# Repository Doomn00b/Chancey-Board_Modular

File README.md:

# Chancey-Board_Modular
A fork of Riskable's great Hall-effect Keyboard, but 100% and modular.

Planned changes are a new RISC-V micro-controller, with more IO, since a 100% implementation will require more.

# The original Riskey-board

Link to repository:
https://github.com/riskable/void_switch_65_pct

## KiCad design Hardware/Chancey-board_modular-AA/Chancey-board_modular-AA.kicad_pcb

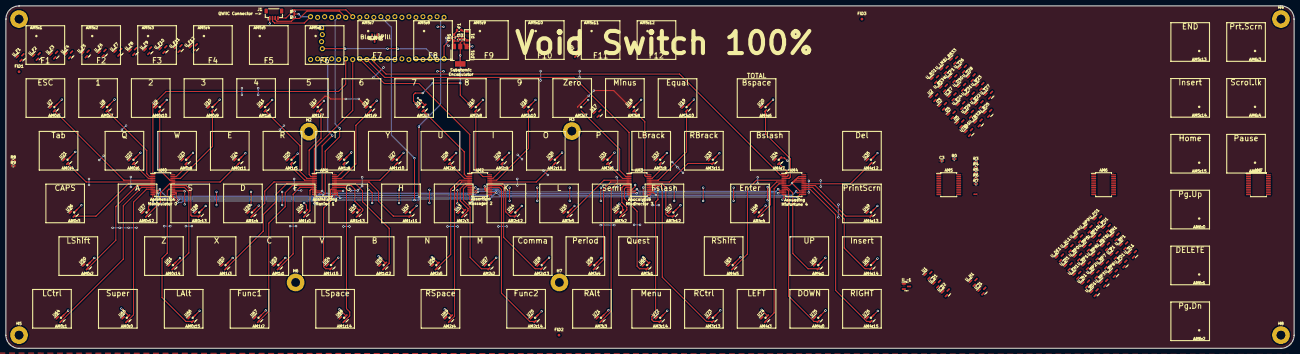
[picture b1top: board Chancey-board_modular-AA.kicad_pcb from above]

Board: 2 copper layers, 465.9 x 123.8 mm, 268 parts (1 on the bottom side), 139 nets.

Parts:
AM0, AM1, AM2, AM3, AM4, AM5, AM6, AM7: CD74HC4067SM; SSOP-24_5.3x8.2mm_P0.65mm
AM0:0: Super; VoidSwitch_1u_SMD
AM0:1: LCtrl; VoidSwitch_1u_SMD
AM0:2: LShift; VoidSwitch_1u_SMD
AM0:3: CAPS; VoidSwitch_1u_SMD
AM0:4: Tab; VoidSwitch_1u_SMD
AM0:5: ESC; VoidSwitch_1u_SMD
AM0:6: Q; VoidSwitch_1u_SMD
AM0:7: 1; VoidSwitch_1u_SMD
AM0:8: W; VoidSwitch_1u_SMD
AM0:9: 3; VoidSwitch_1u_SMD
AM0:10: 2; VoidSwitch_1u_SMD
AM0:11: E; VoidSwitch_1u_SMD
AM0:12: A; VoidSwitch_1u_SMD
AM0:13: S; VoidSwitch_1u_SMD
AM0:14: Z; VoidSwitch_1u_SMD
AM0:15: LAlt; VoidSwitch_1u_SMD
AM1:0: F; VoidSwitch_1u_SMD
AM1:1: C; VoidSwitch_1u_SMD
AM1:2: Func1; VoidSwitch_1u_SMD
AM1:3: X; VoidSwitch_1u_SMD
AM1:4: D; VoidSwitch_1u_SMD
AM1:5: R; VoidSwitch_1u_SMD
AM1:6: 4; VoidSwitch_1u_SMD
AM1:7: 5; VoidSwitch_1u_SMD
AM1:8: T; VoidSwitch_1u_SMD
AM1:9: 6; VoidSwitch_1u_SMD
AM1:10: Y; VoidSwitch_1u_SMD
AM1:11: H; VoidSwitch_1u_SMD
AM1:12: B; VoidSwitch_1u_SMD
AM1:13: G; VoidSwitch_1u_SMD
AM1:14: LSpace; VoidSwitch_1u_SMD
AM1:15: V; VoidSwitch_1u_SMD
AM2:2: M; VoidSwitch_1u_SMD
AM2:3: J; VoidSwitch_1u_SMD
AM2:4: RSpace; VoidSwitch_1u_SMD
AM2:5: N; VoidSwitch_1u_SMD
AM2:6: U; VoidSwitch_1u_SMD
AM2:7: 7; VoidSwitch_1u_SMD
AM2:8: 8; VoidSwitch_1u_SMD
AM2:9: I; VoidSwitch_1u_SMD
AM2:10: 9; VoidSwitch_1u_SMD
AM2:11: O; VoidSwitch_1u_SMD
AM2:12: K; VoidSwitch_1u_SMD
AM2:13: Comma; VoidSwitch_1u_SMD
AM2:14: Func2; VoidSwitch_1u_SMD
AM3:1: Quest; VoidSwitch_1u_SMD
AM3:2: Semi; VoidSwitch_1u_SMD
AM3:3: RAlt; VoidSwitch_1u_SMD
AM3:4: Period; VoidSwitch_1u_SMD
AM3:5: L; VoidSwitch_1u_SMD
AM3:6: P; VoidSwitch_1u_SMD
AM3:7: Zero; VoidSwitch_1u_SMD
AM3:8: Minus; VoidSwitch_1u_SMD
AM3:9: LBrack; VoidSwitch_1u_SMD
AM3:10: Equal; VoidSwitch_1u_SMD
AM3:11: RBrack; VoidSwitch_1u_SMD
AM3:12: Fslash; VoidSwitch_1u_SMD
AM3:13: RCtrl; VoidSwitch_1u_SMD
AM3:14: Menu; VoidSwitch_1u_SMD
AM4:0: DOWN; VoidSwitch_1u_SMD
AM4:1: UP; VoidSwitch_1u_SMD
AM4:3: LEFT; VoidSwitch_1u_SMD
AM4:4: Enter; VoidSwitch_1u_SMD
AM4:5: RShift; VoidSwitch_1u_SMD
AM4:6: Bspace; VoidSwitch_1u_SMD
AM4:7: Bslash; VoidSwitch_1u_SMD
AM4:12: Del; VoidSwitch_1u_SMD
AM4:13: PrintScrn; VoidSwitch_1u_SMD
AM4:14, AM5:14: Insert; VoidSwitch_1u_SMD
AM4:15: RIGHT; VoidSwitch_1u_SMD
AM5:1: F1; VoidSwitch_1u_SMD
AM5:2: F2; VoidSwitch_1u_SMD
AM5:3: F3; VoidSwitch_1u_SMD
AM5:4: F4; VoidSwitch_1u_SMD
AM5:5: F5; VoidSwitch_1u_SMD
AM5:6: F6; VoidSwitch_1u_SMD
AM5:7: F7; VoidSwitch_1u_SMD
AM5:8: F8; VoidSwitch_1u_SMD
AM5:9: F9; VoidSwitch_1u_SMD
AM5:10: F10; VoidSwitch_1u_SMD
AM5:11: F11; VoidSwitch_1u_SMD
AM5:12: F12; VoidSwitch_1u_SMD
AM5:13: END; VoidSwitch_1u_SMD
AM5:15: Home; VoidSwitch_1u_SMD
AM6:0: Pg.Up; VoidSwitch_1u_SMD
AM6:1: DELETE; VoidSwitch_1u_SMD
AM6:2: Pg.Dn; VoidSwitch_1u_SMD
AM6:3: Prt.Scrn; VoidSwitch_1u_SMD
AM6:4: Scrol.lk; VoidSwitch_1u_SMD
AM6:5: Pause; VoidSwitch_1u_SMD
C1, C2, C3: 10u; C_0402_1005Metric
D1: B5819W; D_SOD-123
F1: 500mA; Fuse_0603_1608Metric
FB1: 100 @ 100 MHz; L_0805_2012Metric
FID1, FID2, FID3: Fiducial; Fiducial_1mm_Mask2mm
H1, H2, H3, H4, H5, H6, H7, H8: MountingHole_Pad; MountingHole_3.2mm_M3_Pad
J1: QWIIC; JST_SH_BM04B-SRSS-TB_1x04-1MP_P1.00mm_Vertical
LDO1: AMS1117-3.3; SOT-223-3_TabPin2
NT1: NetTie_2; NetTie-2_SMD_Pad0.5mm
QR*****: https://github.com/riskable/void_switch; VoidSwitch_Repo_QR_0.5mm
R0, R1, R2, R3, R4, R5, R6, R7, R8, R9: 2k2; R_0402_1005Metric
U0, U1, U2, U3, U4, U5, U6, U7, U8, U9, U10, U11, U12, U13, U14, U15, U16, U17, U18, U19, U20, U21, U22, U23, U24, U25, U26, U27, U28, U29, U30, U31, U32, U33, U34, U35, U36, U37, U38, U39, U40, U41, U42, U43, U44, U45, U46, U47, U48, U49, U50, U51, U52, U53, U54, U55, U56, U57, U58, U59, U60, U61, U62, U63, U64, U65, U66, U67, U68, U69, U70, U71, U72, U73, U74, U75, U76: Hall_Sensor; SOT-23
UTab1: Hall_Sensor; SOT-23
U_BP1: BlackPill_STLINK
U_BS1, U_BS34: Hall_Sensor; SOT-23
U_D1, U_D2: Hall_Sensor; SOT-23
U_DE1: Hall_Sensor; SOT-23
U_Di1: Hall_Sensor; SOT-23
U_E7, U_E24: Hall_Sensor; SOT-23
U_EN1: Hall_Sensor; SOT-23
U_F1, U_F2, U_F3, U_F4, U_F5, U_F6, U_F7, U_F8, U_F9, U_F10, U_F11, U_F12: Hall_Sensor; SOT-23
U_H1: Hall_Sensor; SOT-23
U_I1, U_I29: Hall_Sensor; SOT-23
U_In1: Hall_Sensor; SOT-23
U_LB32: Hall_Sensor; SOT-23
U_LM1: Hall_Sensor; SOT-23
U_LP1: Hall_Sensor; SOT-23
U_ND1: Hall_Sensor; SOT-23
U_NL1: Hall_Sensor; SOT-23
U_NP0, U_NP1, U_NP2, U_NP3, U_NP4, U_NP5, U_NP6, U_NP7, U_NP8, U_NP9, U_NP10: Hall_Sensor; SOT-23
U_NpT1: Hall_Sensor; SOT-23
U_O30: Hall_Sensor; SOT-23
U_P1, U_P31: Hall_Sensor; SOT-23
U_PD1: Hall_Sensor; SOT-23
U_PS1: Hall_Sensor; SOT-23
U_PU1: Hall_Sensor; SOT-23
U_Q22: Hall_Sensor; SOT-23
U_R25: Hall_Sensor; SOT-23
U_RB33: Hall_Sensor; SOT-23
U_RM1: Hall_Sensor; SOT-23
U_RP1: Hall_Sensor; SOT-23
U_SL1: Hall_Sensor; SOT-23
U_T26: Hall_Sensor; SOT-23
U_U28: Hall_Sensor; SOT-23
U_W23: Hall_Sensor; SOT-23
U_Y27: Hall_Sensor; SOT-23
U_~1: Hall_Sensor; SOT-23

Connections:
+3.3V: AM0.24 (VCC), AM1.24 (VCC), AM2.24 (VCC), AM3.24 (VCC), AM4.24 (VCC), AM5.24 (VCC), AM6.24 (VCC), AM7.24 (VCC), C2.1, C3.1, NT1.2, U0.1 (VDD), U1.1 (VDD), U2.1 (VDD), U3.1 (VDD), U4.1 (VDD), U5.1 (VDD), U6.1 (VDD), U7.1 (VDD), U8.1 (VDD), U9.1 (VDD), U10.1 (VDD), U11.1 (VDD), U12.1 (VDD), U13.1 (VDD), U14.1 (VDD), U15.1 (VDD), U16.1 (VDD), U17.1 (VDD), U18.1 (VDD), U19.1 (VDD), U20.1 (VDD), U21.1 (VDD), U22.1 (VDD), U23.1 (VDD), U24.1 (VDD), U25.1 (VDD), U26.1 (VDD), U27.1 (VDD), U28.1 (VDD), U29.1 (VDD), U30.1 (VDD), U31.1 (VDD), U32.1 (VDD), U33.1 (VDD), U34.1 (VDD), U35.1 (VDD), U36.1 (VDD), U37.1 (VDD), U38.1 (VDD), U39.1 (VDD), U40.1 (VDD), U41.1 (VDD), U42.1 (VDD), U43.1 (VDD), U44.1 (VDD), U45.1 (VDD), U46.1 (VDD), U47.1 (VDD), U48.1 (VDD), U49.1 (VDD), U50.1 (VDD), U51.1 (VDD), U52.1 (VDD), U53.1 (VDD), U54.1 (VDD), U55.1 (VDD), U56.1 (VDD), U57.1 (VDD), U58.1 (VDD), U59.1 (VDD), U60.1 (VDD), U61.1 (VDD), U62.1 (VDD), U63.1 (VDD), U64.1 (VDD), U65.1 (VDD), U66.1 (VDD), U67.1 (VDD), U68.1 (VDD), U69.1 (VDD), U70.1 (VDD), U71.1 (VDD), U72.1 (VDD), U73.1 (VDD), U74.1 (VDD), U75.1 (VDD), U76.1 (VDD), UTab1.1 (VDD), U_BS1.1 (VDD), U_BS34.1 (VDD), U_D1.1 (VDD), U_D2.1 (VDD), U_DE1.1 (VDD), U_Di1.1 (VDD), U_E7.1 (VDD), U_E24.1 (VDD), U_EN1.1 (VDD), U_F1.1 (VDD), U_F2.1 (VDD), U_F3.1 (VDD), U_F4.1 (VDD), U_F5.1 (VDD), U_F6.1 (VDD), U_F7.1 (VDD), U_F8.1 (VDD), U_F9.1 (VDD), U_F10.1 (VDD), U_F11.1 (VDD), U_F12.1 (VDD), U_H1.1 (VDD), U_I1.1 (VDD), U_I29.1 (VDD), U_In1.1 (VDD), U_LB32.1 (VDD), U_LM1.1 (VDD), U_LP1.1 (VDD), U_ND1.1 (VDD), U_NL1.1 (VDD), U_NP0.1 (VDD), U_NP1.1 (VDD), U_NP2.1 (VDD), U_NP3.1 (VDD), U_NP4.1 (VDD), U_NP5.1 (VDD), U_NP6.1 (VDD), U_NP7.1 (VDD), U_NP8.1 (VDD), U_NP9.1 (VDD), U_NP10.1 (VDD), U_NpT1.1 (VDD), U_O30.1 (VDD), U_P1.1 (VDD), U_P31.1 (VDD), U_PD1.1 (VDD), U_PS1.1 (VDD), U_PU1.1 (VDD), U_Q22.1 (VDD), U_R25.1 (VDD), U_RB33.1 (VDD), U_RM1.1 (VDD), U_RP1.1 (VDD), U_SL1.1 (VDD), U_T26.1 (VDD), U_U28.1 (VDD), U_W23.1 (VDD), U_Y27.1 (VDD), U_~1.1 (VDD)
+3.3V_QWIIC: J1.2, R1.1, R2.1, U_BP1.20 (3V3)
+5V: D1.2 (A), U_BP1.40 (5V)
/AM0: AM0.1 (COM), U_BP1.26 (PA0)
/AM0:0: AM0.9 (I0), U65.2 (OUT)
/AM0:1: AM0.8 (I1), U64.2 (OUT)
/AM0:2: AM0.7 (I2), U50.2 (OUT)
/AM0:3: AM0.6 (I3), U36.2 (OUT)
/AM0:4: AM0.5 (I4), U21.2 (OUT), UTab1.2 (OUT)
/AM0:5: AM0.4 (I5), U_E7.2 (OUT)
/AM0:6: AM0.3 (I6), U22.2 (OUT), U_Q22.2 (OUT)
/AM0:7: AM0.2 (I7), U1.2 (OUT)
/AM0:8: AM0.23 (I8), U23.2 (OUT), U_W23.2 (OUT)
/AM0:9: AM0.22 (I9), U3.2 (OUT), U10.2 (OUT)
/AM0:10: AM0.21 (I10), U2.2 (OUT)
/AM0:11: AM0.20 (I11), U24.2 (OUT), U_E24.2 (OUT)
/AM0:12: AM0.19 (I12), U37.2 (OUT)
/AM0:13: AM0.18 (I13), U38.2 (OUT)
/AM0:14: AM0.17 (I14), U51.2 (OUT)
/AM0:15: AM0.16 (I15), U66.2 (OUT)
/AM1: AM1.1 (COM), U_BP1.27 (PA1)
/AM1:0: AM1.9 (I0), U40.2 (OUT)
/AM1:1: AM1.8 (I1), U53.2 (OUT)
/AM1:2: AM1.7 (I2), U67.2 (OUT)
/AM1:3: AM1.6 (I3), U52.2 (OUT)
/AM1:4: AM1.5 (I4), U39.2 (OUT)
/AM1:5: AM1.4 (I5), U25.2 (OUT), U_R25.2 (OUT)
/AM1:6: AM1.3 (I6), U4.2 (OUT), U11.2 (OUT)
/AM1:7: AM1.2 (I7), U5.2 (OUT), U12.2 (OUT)
/AM1:8: AM1.23 (I8), U26.2 (OUT), U_T26.2 (OUT)
/AM1:9: AM1.22 (I9), U6.2 (OUT), U13.2 (OUT)
/AM1:10: AM1.21 (I10), U27.2 (OUT), U_Y27.2 (OUT)
/AM1:11: AM1.20 (I11), U42.2 (OUT)
/AM1:12: AM1.19 (I12), U55.2 (OUT)
/AM1:13: AM1.18 (I13), U41.2 (OUT)
/AM1:14: AM1.17 (I14), U68.2 (OUT)
/AM1:15: AM1.16 (I15), U54.2 (OUT)
/AM2: AM2.1 (COM), U_BP1.28 (PA2)
/AM2:0: AM2.9 (I0), U_~1.2 (OUT)
/AM2:2: AM2.7 (I2), U57.2 (OUT)
/AM2:3: AM2.6 (I3), U43.2 (OUT)
/AM2:4: AM2.5 (I4), U69.2 (OUT)
/AM2:5: AM2.4 (I5), U56.2 (OUT)
/AM2:6: AM2.3 (I6), U28.2 (OUT), U_U28.2 (OUT)
/AM2:7: AM2.2 (I7), U7.2 (OUT), U14.2 (OUT)
/AM2:8: AM2.23 (I8), U8.2 (OUT), U15.2 (OUT)
/AM2:9: AM2.22 (I9), U29.2 (OUT), U_I29.2 (OUT)
/AM2:10: AM2.21 (I10), U9.2 (OUT), U16.2 (OUT)
/AM2:11: AM2.20 (I11), U30.2 (OUT), U_O30.2 (OUT)
/AM2:12: AM2.19 (I12), U44.2 (OUT)
/AM2:13: AM2.18 (I13), U58.2 (OUT)
/AM2:14: AM2.17 (I14), U70.2 (OUT)
/AM3: AM3.1 (COM), U_BP1.29 (PA3)
/AM3:1: AM3.8 (I1), U60.2 (OUT)
/AM3:2: AM3.7 (I2), U46.2 (OUT)
/AM3:3: AM3.6 (I3), U71.2 (OUT)
/AM3:4: AM3.5 (I4), U59.2 (OUT)
/AM3:5: AM3.4 (I5), U45.2 (OUT)
/AM3:6: AM3.3 (I6), U31.2 (OUT), U_P31.2 (OUT)
/AM3:7: AM3.2 (I7), U0.2 (OUT), U17.2 (OUT)
/AM3:8: AM3.23 (I8), U18.2 (OUT), U_LM1.2 (OUT)
/AM3:9: AM3.22 (I9), U32.2 (OUT), U_LB32.2 (OUT)
/AM3:10: AM3.21 (I10), U19.2 (OUT), U_LP1.2 (OUT)
/AM3:11: AM3.20 (I11), U33.2 (OUT), U_RB33.2 (OUT)
/AM3:12: AM3.19 (I12), U47.2 (OUT)
/AM3:13: AM3.18 (I13), U73.2 (OUT)
/AM3:14: AM3.17 (I14), U72.2 (OUT)
/AM4: AM4.1 (COM), U_BP1.30 (PA4)
/AM4:0: AM4.9 (I0), U75.2 (OUT)
/AM4:1: AM4.8 (I1), U62.2 (OUT)
/AM4:3: AM4.6 (I3), U74.2 (OUT)
/AM4:4: AM4.5 (I4), U48.2 (OUT)
/AM4:5: AM4.4 (I5), U61.2 (OUT)
/AM4:6: AM4.3 (I6), U20.2 (OUT), U_BS1.2 (OUT)
/AM4:7: AM4.2 (I7), U34.2 (OUT), U_BS34.2 (OUT)
/AM4:12: AM4.19 (I12), U35.2 (OUT)
/AM4:13: AM4.18 (I13), U49.2 (OUT)
/AM4:14: AM4.17 (I14), U63.2 (OUT)
/AM4:15: AM4.16 (I15), U76.2 (OUT)
/AM5: AM5.1 (COM), U_BP1.24 (PC15)
/AM5:1: AM5.8 (I1), U_F1.2 (OUT)
/AM5:2: AM5.7 (I2), U_F2.2 (OUT)
/AM5:3: AM5.6 (I3), U_F3.2 (OUT)
/AM5:4: AM5.5 (I4), U_F4.2 (OUT)
/AM5:5: AM5.4 (I5), U_F5.2 (OUT)
/AM5:6: AM5.3 (I6), U_F6.2 (OUT)
/AM5:7: AM5.2 (I7), U_F7.2 (OUT)
/AM5:8: AM5.23 (I8), U_F8.2 (OUT)
/AM5:9: AM5.22 (I9), U_F9.2 (OUT)
/AM5:10: AM5.21 (I10), U_F10.2 (OUT)
/AM5:11: AM5.20 (I11), U_F11.2 (OUT)
/AM5:12: AM5.19 (I12), U_F12.2 (OUT)
/AM5:13: AM5.18 (I13), U_EN1.2 (OUT)
/AM5:14: AM5.17 (I14), U_In1.2 (OUT)
/AM5:15: AM5.16 (I15), U_H1.2 (OUT)
/AM6: AM6.1 (COM), U_BP1.36 (PB2)
/AM6:0: AM7.9 (I0), U_PU1.2 (OUT)
/AM6:1: AM7.8 (I1), U_DE1.2 (OUT)
/AM6:2: AM7.7 (I2), U_PD1.2 (OUT)
/AM6:3: AM7.6 (I3), U_PS1.2 (OUT)
/AM6:4: AM7.5 (I4), U_SL1.2 (OUT)
/AM6:5: AM7.4 (I5), U_P1.2 (OUT)
/AM6:6: AM7.3 (I6), U_NL1.2 (OUT)
/AM6:7: AM7.2 (I7), U_Di1.2 (OUT)
/AM6:8: AM7.23 (I8), U_NpT1.2 (OUT)
/AM6:9: AM7.22 (I9), U_RM1.2 (OUT)
/AM6:10: AM7.21 (I10), U_NP4.2 (OUT)
/AM6:11: AM7.20 (I11), U_NP5.2 (OUT)
/AM6:12: AM7.19 (I12), U_NP6.2 (OUT)
/AM6:13: AM7.18 (I13), U_NP1.2 (OUT)
/AM6:14: AM7.17 (I14), U_NP2.2 (OUT)
/AM6:15: AM7.16 (I15), U_NP3.2 (OUT)
/AM7: AM7.1 (COM), U_BP1.22 (PC13)
/AM7:0: AM6.9 (I0), U_NP7.2 (OUT)
/AM7:1: AM6.8 (I1), U_NP8.2 (OUT)
/AM7:2: AM6.7 (I2), U_NP9.2 (OUT)
/AM7:3: AM6.6 (I3), U_RP1.2 (OUT)
/AM7:4: AM6.5 (I4), U_NP0.2 (OUT)
/AM7:5: AM6.4 (I5), U_ND1.2 (OUT)
/AM7:6: AM6.3 (I6), U_NP10.2 (OUT)
/Analog Multiplexers/MX-PD0: AM0.15 (~E), R0.2
/Analog Multiplexers/MX-PD1: AM1.15 (~E), R4.2
/Analog Multiplexers/MX-PD2: AM2.15 (~E), R3.2
/Analog Multiplexers/MX-PD3: AM3.15 (~E), R5.1
/Analog Multiplexers/MX-PD4: AM4.15 (~E), R6.1
/Analog Multiplexers/MX-PD5: AM5.15 (~E), R7.1
/Analog Multiplexers/MX-PD6: AM6.15 (~E), AM7.15 (~E), R8.1, R9.1
/SELECT0: AM0.10 (S0), AM1.10 (S0), AM2.10 (S0), AM3.10 (S0), AM4.10 (S0), AM5.10 (S0), AM6.10 (S0), AM7.10 (S0), U_BP1.23 (PC14)
/SELECT1: AM0.11 (S1), AM1.11 (S1), AM2.11 (S1), AM3.11 (S1), AM4.11 (S1), AM5.11 (S1), AM6.11 (S1), AM7.11 (S1), U_BP1.16 (PB8)
/SELECT2: AM0.14 (S2), AM1.14 (S2), AM2.14 (S2), AM3.14 (S2), AM4.14 (S2), AM5.14 (S2), AM6.14 (S2), AM7.14 (S2), U_BP1.1 (PB12)
/SELECT3: AM0.13 (S3), AM1.13 (S3), AM2.13 (S3), AM3.13 (S3), AM4.13 (S3), AM5.13 (S3), AM6.13 (S3), AM7.13 (S3), U_BP1.10 (PA15)
AM5:15: U_D1.2 (OUT), U_D2.2 (OUT)
GND: AM0.12 (GND), AM1.12 (GND), AM2.12 (GND), AM3.12 (GND), AM4.12 (GND), AM5.12 (GND), AM6.12 (GND), AM7.12 (GND), C1.2, C2.2, C3.2, H1.1, H2.1, H3.1, H4.1, H5.1, H6.1, H7.1, H8.1, J1.1, LDO1.1 (GND), R0.1, R3.1, R4.1, R5.2, R6.2, R7.2, R8.2, R9.2, U0.3 (GND), U1.3 (GND), U2.3 (GND), U3.3 (GND), U4.3 (GND), U5.3 (GND), U6.3 (GND), U7.3 (GND), U8.3 (GND), U9.3 (GND), U10.3 (GND), U11.3 (GND), U12.3 (GND), U13.3 (GND), U14.3 (GND), U15.3 (GND), U16.3 (GND), U17.3 (GND), U18.3 (GND), U19.3 (GND), U20.3 (GND), U21.3 (GND), U22.3 (GND), U23.3 (GND), U24.3 (GND), U25.3 (GND), U26.3 (GND), U27.3 (GND), U28.3 (GND), U29.3 (GND), U30.3 (GND), U31.3 (GND), U32.3 (GND), U33.3 (GND), U34.3 (GND), U35.3 (GND), U36.3 (GND), U37.3 (GND), U38.3 (GND), U39.3 (GND), U40.3 (GND), U41.3 (GND), U42.3 (GND), U43.3 (GND), U44.3 (GND), U45.3 (GND), U46.3 (GND), U47.3 (GND), U48.3 (GND), U49.3 (GND), U50.3 (GND), U51.3 (GND), U52.3 (GND), U53.3 (GND), U54.3 (GND), U55.3 (GND), U56.3 (GND), U57.3 (GND), U58.3 (GND), U59.3 (GND), U60.3 (GND), U61.3 (GND), U62.3 (GND), U63.3 (GND), U64.3 (GND), U65.3 (GND), U66.3 (GND), U67.3 (GND), U68.3 (GND), U69.3 (GND), U70.3 (GND), U71.3 (GND), U72.3 (GND), U73.3 (GND), U74.3 (GND), U75.3 (GND), U76.3 (GND), UTab1.3 (GND), U_BP1.19 (GND), U_BP1.39 (GND), U_BP1.44 (GND), U_BS1.3 (GND), U_BS34.3 (GND), U_D1.3 (GND), U_D2.3 (GND), U_DE1.3 (GND), U_Di1.3 (GND), U_E7.3 (GND), U_E24.3 (GND), U_EN1.3 (GND), U_F1.3 (GND), U_F2.3 (GND), U_F3.3 (GND), U_F4.3 (GND), U_F5.3 (GND), U_F6.3 (GND), U_F7.3 (GND), U_F8.3 (GND), U_F9.3 (GND), U_F10.3 (GND), U_F11.3 (GND), U_F12.3 (GND), U_H1.3 (GND), U_I1.3 (GND), U_I29.3 (GND), U_In1.3 (GND), U_LB32.3 (GND), U_LM1.3 (GND), U_LP1.3 (GND), U_ND1.3 (GND), U_NL1.3 (GND), U_NP0.3 (GND), U_NP1.3 (GND), U_NP2.3 (GND), U_NP3.3 (GND), U_NP4.3 (GND), U_NP5.3 (GND), U_NP6.3 (GND), U_NP7.3 (GND), U_NP8.3 (GND), U_NP9.3 (GND), U_NP10.3 (GND), U_NpT1.3 (GND), U_O30.3 (GND), U_P1.3 (GND), U_P31.3 (GND), U_PD1.3 (GND), U_PS1.3 (GND), U_PU1.3 (GND), U_Q22.3 (GND), U_R25.3 (GND), U_RB33.3 (GND), U_RM1.3 (GND), U_RP1.3 (GND), U_SL1.3 (GND), U_T26.3 (GND), U_U28.3 (GND), U_W23.3 (GND), U_Y27.3 (GND), U_~1.3 (GND)
unnamed: D1.1 (K), F1.1
unnamed: F1.2, FB1.2
unnamed: C1.1, FB1.1, LDO1.3 (VI)
unnamed: LDO1.2 (VO), NT1.1
PB6_SCL1: J1.4, R1.2, U_BP1.14 (PB6)
PB7_SDA1: J1.3, R2.2, U_BP1.15 (PB7)

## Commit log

2023-06-07 First upload. Added more sensors, switches and multiplexers.
2023-06-07 Changed many global labels to hierarchical and local labels.
